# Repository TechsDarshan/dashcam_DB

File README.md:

# Dashcam Daughter board(DDB)

The Dashcam Daughter Board is a sub-board of the Dashcam project. It controls the neopixel indicators, includes a buzzer, and houses a reset button.

## Connection:

At Daughter Board:
| JST- DDB | Jetson Nano |
|--|--|
| +5v | +5v |
|LED Selector|GPIO15|
| ValuePin_1|GPIO16|
|ValuePin_2|GPIO18|
|Push button |GPIO19|
|Buzzer|GPIO20|
|NC||
|GND|GND|

# Code Building:

## Attiny85 is flashed with neo.ino

Use the 6 pin ISP programming port to flash/change the code.

##LED Controller library can be called to control the state LEDs 1 & 2.

### Installation

To use the LED Controller library in your project, simply include the `ledcontroller.py` file in your project directory.

### Usage

Import the `ledcontroller` module in your Python script to gain access to the `setcolor()` function. Use this function to control the state of LEDs 1 and 2 by specifying the LED index and desired color.

### Functionality

#### `setcolor(index, color)`

Set the color of the specified LED.

- `index`: 0 for LED 1, 1 for LED 2.
- `color`: Available options - NONE, RED, GREEN, ORANGE.

### Example code

````python
from LEDController import LEDController
  import time
  print("Starting demo now! Press CTRL+C to exit")
  leds = LEDController()
  for led in (0, 1):
    for color in LEDController.COLORS:
      print('Setting LED {} to {}'.format(led, color))
      leds.setColor(led, color)
      time.sleep(1)
      ```
````

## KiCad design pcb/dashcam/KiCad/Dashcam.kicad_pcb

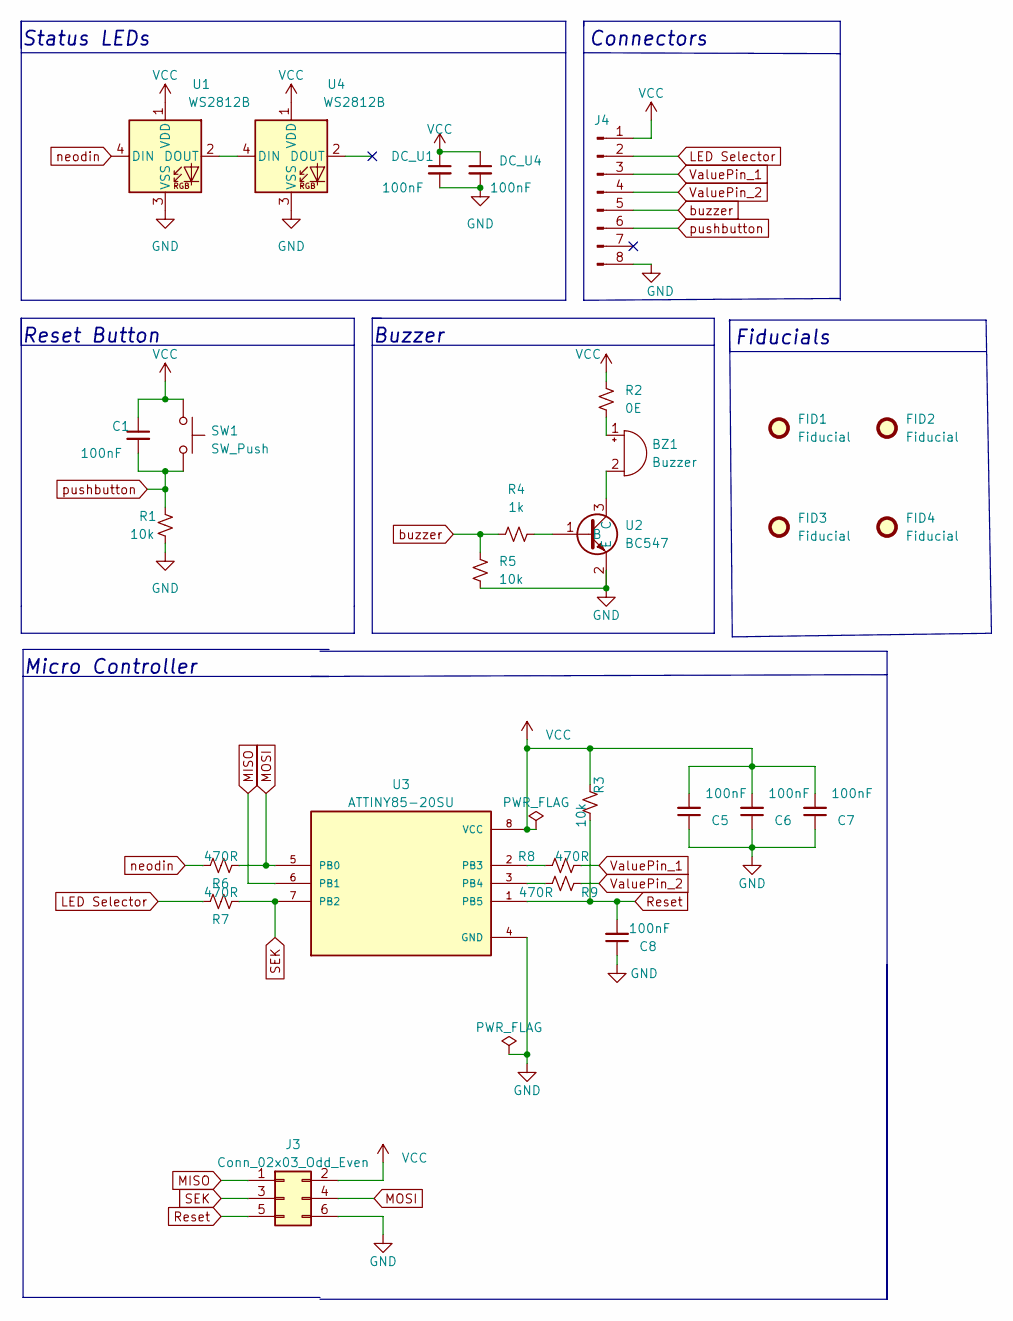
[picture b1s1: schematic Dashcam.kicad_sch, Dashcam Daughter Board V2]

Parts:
BZ1: Buzzer; Buzzer_12x9.5RM7.6
C1, C5, C6, C7, C8: 100nF; C_0603_1608Metric
DC_U1, DC_U4: 100nF; C_0603_1608Metric
FID1, FID2, FID3, FID4: Fiducial; Fiducial_1mm_Mask2mm
J3: Conn_02x03_Odd_Even; PinHeader_2x03_P1.00mm_Vertical
J4: Conn_01x08_Pin; JST_GH_BM08B-GHS-TBT_1x08-1MP_P1.25mm_Vertical
R1, R3, R5: 10k; R_0603_1608Metric
R2: 0E; R_0603_1608Metric
R4: 1k; R_0603_1608Metric
R6, R7, R8, R9: 470R; R_0603_1608Metric
SW1: SW_Push; SW_SPST_B3U-3000P
U1, U4: WS2812B; LED_WS2812B_PLCC4_5.0x5.0mm_P3.2mm
U2: BC547; SOT-23
U3: ATTINY85-20SU; SOIC127P798X216-8N; PARTREV 2586Q–AVR–08/2013

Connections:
+5V: C1.1, C5.2, C6.2, C7.2, DC_U1.1, DC_U4.1, J3.2, J4.1, R2.1, R3.2, SW1.2, U1.1 (VDD), U3.8 (VCC), U4.1 (VDD)
GND: C5.1, C6.1, C7.1, C8.1, DC_U1.2, DC_U4.2, J3.6, J4.8, R1.2, R5.1, U1.3 (VSS), U2.2 (E), U3.4 (GND), U4.3 (VSS)
LED Selector: J4.2, R7.1
MISO: J3.1, U3.6 (PB1)
MOSI: J3.4, R6.2, U3.5 (PB0)
unnamed: BZ1.2 (+), U2.3 (C)
unnamed: BZ1.1 (-), R2.2
unnamed: U1.2 (DOUT), U4.4 (DIN)
unnamed: R4.2, U2.1 (B)
unnamed: R8.1, U3.2 (PB3)
unnamed: R9.1, U3.3 (PB4)
Reset: C8.2, J3.5, R3.1, U3.1 (PB5)
SEK: J3.3, R7.2, U3.7 (PB2)
ValuePin_1: J4.3, R8.2
ValuePin_2: J4.4, R9.2
buzzer: J4.5, R4.1, R5.2
neodin: R6.1, U1.4 (DIN)
pushbutton: C1.2, J4.6, R1.1, SW1.1

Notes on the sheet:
Status LEDs
Buzzer
Micro Controller
Fiducials
Reset Button
Connectors

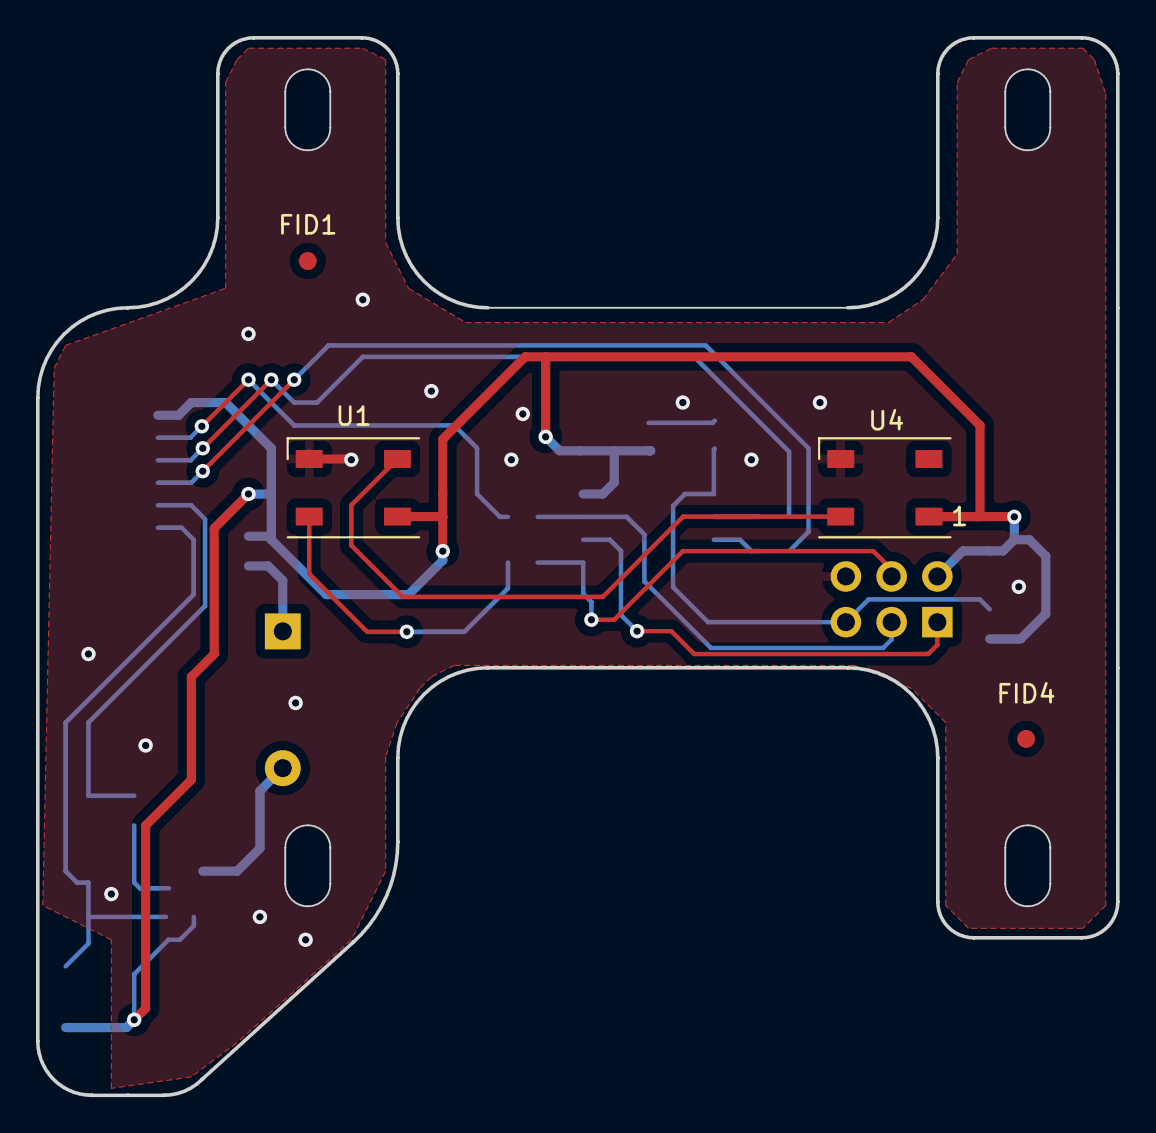
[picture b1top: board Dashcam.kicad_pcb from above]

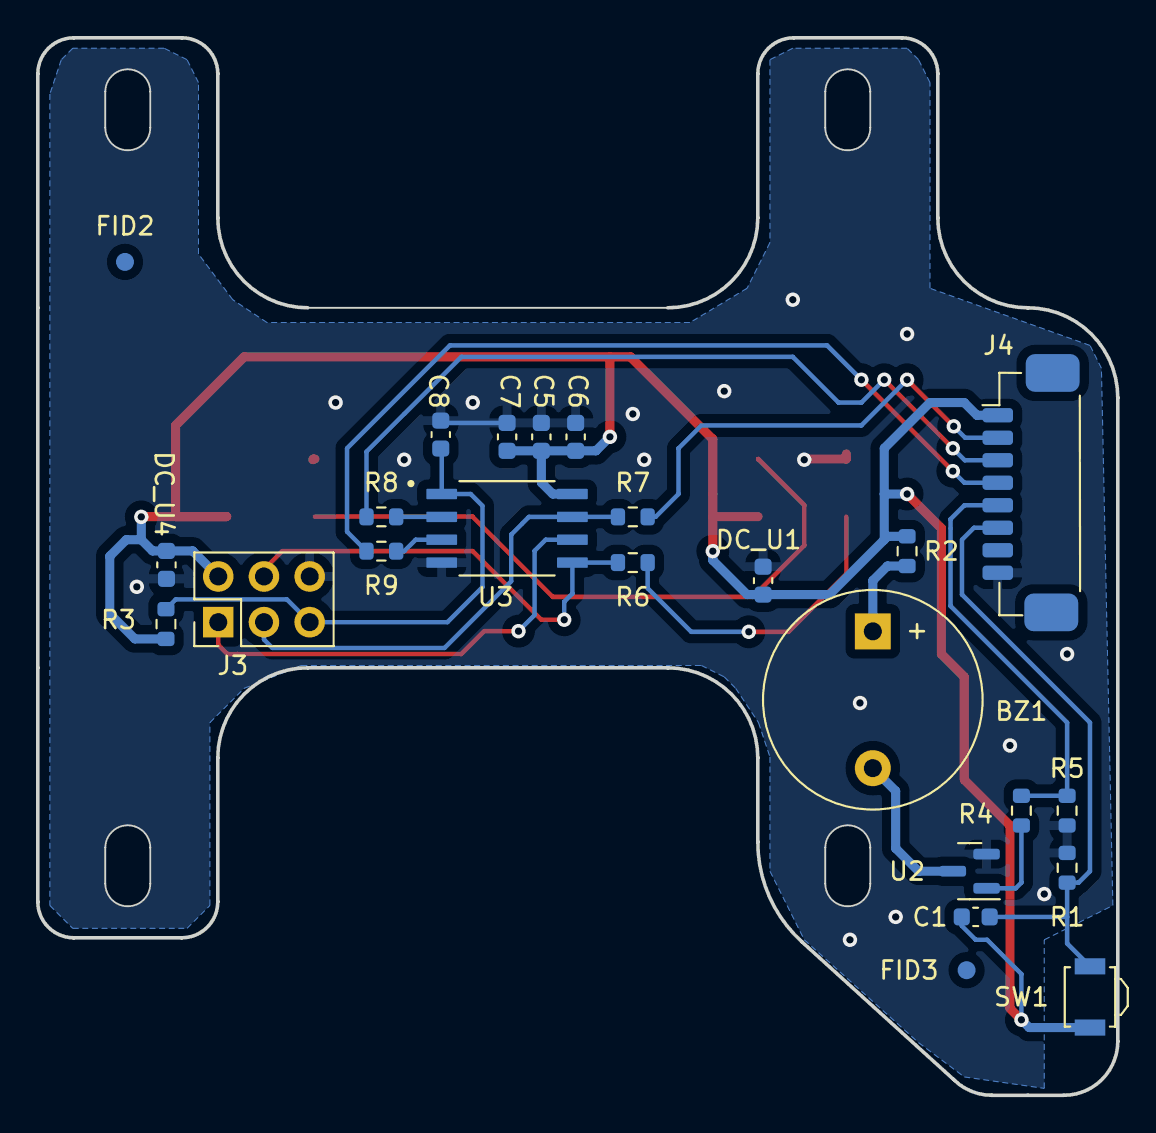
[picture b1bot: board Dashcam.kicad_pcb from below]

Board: 2 copper layers, 60.0 x 58.8 mm, 28 parts (24 on the bottom side), 18 nets.

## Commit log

2024-01-06 README.md edit
2024-01-06 edit readme
2024-01-08 diode removed added cap to push reset ckt
2024-01-09 pcb- pulldown removed, 470 ohm added in series
2024-01-10 added gerber files and changed 2x3 connector
2024-01-11 comit
2024-01-17 commit test
2024-01-17 test2
2024-01-17 test3
2024-01-17 test5
2024-01-17 added cpplint and clang format
2024-01-17 Fix github actions: Install cpplint
2024-03-20 edited gpios
2024-03-20 removed previous pdf
